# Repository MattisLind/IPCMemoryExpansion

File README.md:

# HP Integral PC Memory Expansion board

The HP Integral PC was a portable 68000 UNIX based computer introduced in 1984. The computer included a floppy drive as mass storage and a printer was built in. The screen was a electroluminicent screen. The computer has a HPIB connector to attach to external devices. External disks can be attached through HPIB.

The computer has a two expansion slot where various peripherals can be installed. For example serial boards or memory expansion boards. It was also possible to install ROM boards. The software engineering ROM has 2Mbyte of ROM expansion and when installed appear as 8 disk devices in the Unix system.

The project aims at creating a 7M RAM and 8M ROM memory expansion to the HP Integral computer. RAM is implemented using a single SRAM chip and ROM is implemented using a single NOR FLASH ROM chip. DIP-switches are used to map the ROM into the various ROM areas of the Integral.

## Levelshifting

All signals are level shifted from 5V TTL to 3.3V LVTTL using six 74LVC245 which has 5V tolerant inputs. The two open-collector signals, NBDTACK and NBIMA is handled by 1 74LS38 chip.

## Address decoding

A Xilinx XC2C32A CPLD is used for all address decoding and ROM remapping. The VHDL is provided [here](https://raw.githubusercontent.com/MattisLind/IPCMemoryExpansion/main/XILINX/IntegralMemExp/main.vhd).

## DIPSWITCH

The board is using a piano-type dipswitch for easy access from the side. When the switch is in the up position in corresponds to the off condition or digital 1 signal. When the switch is in the down position this corresponds to a on condition or 0 signal. X means that the position of the switch is irrelevant.

DIPSW0 to DIPSW5 is used for controlling the ROM mapping in the address space.

DIPSW7 is used for enabling and disabling the busdrivers and DIPSW6 is connected to RESET of the processor. Thus the processor portion can be completely disabled when both these switches are pushed down (on). They should be in the UP (off) position so that the processor runs and can access the memory when trying to upload to the flash memory onboard. When used in the Integral PC they should be in the DOWN (on) position to stop the processor and disable processor access to the memory.

## ROM
The mapping of the FLASH ROM memory is controlled by six dipswitches as follows:

| Integral address range | DIPSW0 | DIPSW1 | DIPSW2 | DIPSW3 | DIPSW4 | DIPSW5 | Flash memory range | Used for |
|------------------------|--------|--------|--------|--------|--------|--------|--------------------|----------|
| 000000 - 07FFFF        |   Down(0)    |   Down(0)    |   X    |   X    |   X    |   X    |  000000-07FFFF     | SYS V ROM|
| 000000 - 07FFFF        |   Down(0)    |   Up(1)    |   X    |   X    |   X    |   X    |  080000-0FFFFF     | DiagA ROM|
| 000000 - 07FFFF        |   Up(1)    |   Down(0)    |   X    |   X    |   X    |   X    |  100000-17FFFF     | DiagB ROM|
| 000000 - 07FFFF        |   Up(1)    |   Up(1)    |   X    |   X    |   X    |   X    |  NONE    | Internal ROM used |
| 080000 - 0FFFFF        |   X    |   X    |   Down(0)    |   X    |   X    |   X    |  NONE     | NONE |
| 080000 - 0FFFFF        |   X    |   X    |   Up(1)    |   X    |   X    |   X    |  180000-1FFFFF     | BASIC ROM |
| 100000 - 1FFFFF        |   X    |   X    |   X    |   X    |   X    |   Down(0)    |  NONE              |           |
| 100000 - 1FFFFF        |   X    |   X    |   X    |   X    |   X    |   Up(1)    |  600000-6FFFFF     | AUX ROM 3|
| 200000 - 3FFFFF        |   X    |   X    |   X    |   Down(0)    |   Down(0)    |   X    |  200000-3FFFFF     | SE ROM |
| 200000 - 3FFFFF        |   X    |   X    |   X    |   Down(0)    |   Up(1)    |   X    |  400000-5FFFFF     | AUX ROM 1|
| 200000 - 3FFFFF        |   X    |   X    |   X    |   Up(1)    |   X    |   X    |  NONE     | NONE |
| 300000 - 4FFFFF        |   X    |   X    |   X    |   X    |   X    |   Down(0)    |  NONE     | NONE |
| 300000 - 4FFFFF        |   X    |   X    |   X    |   X    |   X    |   Up(1)    |  700000-7FFFFF     | AUX ROM 2 |

There is a STM32F407ZET SoC makes the board look like a USB stick when the USB port is connected to a host computer. 

The ROM is implemented in one single 8 Mbyte SST38VF6401 chip.

## RAM

Normally Integral memory is implemented using memory board sized up to 1 MByte. Each memory board responds to a read port which provide an ID for the board and a writable base address register. The Integral will use these to identfiy each memory board and configure its starting address. However the memory sizing of HP-UX system is completely independent of the memory configuration descibed preiously meaning that these configuaration is not necessary to get the Integral to detect the full memory. This has been verified using the MAME emulation of the Integral.

All this obviously that it would be very much easier to implement a RAM expansion board since it only requires that it would match the RAM address range 800000-EFFFFF.

The RAM is implemented in one single AS6C6416 4M x 16 SRAM memory chip. 

## Testing and design fault finding.

Obviously when testing the board for the first time it didn't work at all. Of course I tested many different ways to get it working. But in the end I think that one main problem was the use of UDS/LDS instead of AS strobe. On the standard 68000 that would probably have worked just fine. But on the HP Integral he AS strobe is not at all the AS strobe from the processor. It has gone through plenty of logic until the AS signal found in the expasion connector is generated. Thus the use of the AS signal is a must. Gating with that signal made the RAM expansio work fine.

Since the 74LVC245 inputs are CMOS there wil be no current flowing towards the expansion board. When I attached a bus extender board to be able to measure on the board the added buslength seemed to cause trouble. Adding bus terminating resistors at the 74LVC245 inputs seemed to fix the issue. To better adapt the 74LVC245 driver to the bus impedance a low ohm resistor was inserted in the bus line path for the data bus.

All these changes resulted in a second spin of the board.

## Spin 2

Spin 1 became quite messy when trying to fix all small problems so I decided on a spin 2. I also added test points to make it easier to measure on the board, a major issue on the first spin was that it was so hard to take measurements. After spin 2 came back from the JLCPCB I found that it was virtually impossible to get hold of the STM32 chip and the CPLD, so the project got dormant until sping 2023 when I eventually was able to order chips.

There were some small changes made to the CPLD VHDL code for spin 2 ~~which to this date has not yet been tested (2023-07-24). I hope to be able to test the board soon.~~
Spin 2 has now been tested and appears to work correctly. Follow instructions further down to install the board.

## Firmware

There are two firmwares. One Arduino style .ino-sketch which I used for testing and the a STM32Cube applicaton that is the production code. I used STM32 because it was so simple to wrap up the USB mass storage stuff. The code essentially enables the FSMC controller of the chip and enables the USB mass storage code, then it responds to read and writes to the memory. While the USB-cable is connected the green LED will blink. The yellow LED will blink when a read is performed and the red will blink when a write is performed.

## Installation

There are three steps that need to be taken to install the all needed software/firmware to get the board running.
1. Program the CPLD
2. Install the STM32 firmware
3. Upload integral software to the board

For all these steps the USB connector of the board need to be connected to a USB outlet to the computer. This will thus supply the board with power and in the third step also make the board able to communicate with the host.

### Program the CPLD

The CPLD code is written in VHDL and I have used the Xilinx ISE version 14.7. In order to just install the existing JEDEC file provided in the repo it is only necessary to use the Impact tool in the Xilinx ISE suite. Download, start Impact, attach the Xilinx download cable and make sure that the device is detected. Then select the main.jed file and program the device.

### Install the STM32 firmware

You need both the STM32CubeIDE and STM32CubeProgrammer which has to be downloaded from the ST webpage. Use defaults when installing the software.

When installation is ready start STM32CubeIDE and select the "Open Projects from file System" option in the menu. Select the folder " Software/STM32CubeIDE/workspace_1.7.0 /HP IPC Memory Expansion/" in this repo. In the project menu, select the Build Configurations. This will open a submenu which where you can do "Set Active" Select "Release"

Now do "Build All" from the project menu and the full software will be built.

Now start the STM32CubeProgrammer software nd make sure the STM32 download canle is attached to the board and that power is supplied to the board using the USB cable. In this step DIPSW 6 and DIPSW 7 has to be in the up posistion.

Select the "HP IPC Memory Expansion.elf" binary in the Release folder and do a "Erase and program" operation.

### Uploading Integral software to the board

The idea is to use the Linux dd command to transfer the image-file generated by the build.sh shellscript in ROMS folder. When doing so the red and green LEDs should blink. It should also be possible to read back the content stored using dd and compare with the actual file. It is important to write the image to the topmost 8M of the USB device created when the board is connected over USB. The top 8M is mapped to the flash memory while the lower 8M is mapped to the SRAM.

Thus this command is needed to write the flash:

```
sudo dd if=flash_image.bin of=/dev/sd<x> bs=1k seek=8192
```
where ```/dev/sd<x>``` is the device that is allocated for the mass storage device that the board is acting as. Check using ```dmesg``` what device is created when it is plugged into the USB-port.

## Schematic 

## Install instructions by Carl Claunch

After spin 1 was completed I was not able to get components for spin 2 although the board had been fabricated. All this due to the post-covid semiconductor crunch. In July 2023 I got contacted by Carl who had been asked to help out to do the installation of the firmware. As we sorted out how topoerform the steps (which I had more or less forgotten since I initially designed it) he created a nice document which describes the steps do be done. I link it below:

[Install instructions by Carl Claunch](https://github.com/MattisLind/IPCMemoryExpansion/blob/main/HP%20Integral%20board%20instructions.pdf)

## BOM
This is a BOM for the spin 2 board:

| Component designator | Description | Mouser order number | Misc. |
|----------------------|-------------|---------------------|-------|
| R1,R5,R6,R7,R8,R9,R11,R14,R15| 10kOhm SMD 0805 |  -  |   |
| R2,R3,R4        | 330 Ohm SMD 0805 | - | |
| R10 | 1MOhm SMD 0805 | - | |
| R12,R13 | 22 Ohm SMD 0805 | - | |
| RN1,RN2,RN15,RN16 |  network 4 x bussed 56 Ohm THT | 652-4608X-2LF-56 | |
| RN3,RN4,RN5,RN6,RN11,RN12 | network 8 x star 3.9 KOhm  THT | 652-4609X-1LF-3.9K | |
| RN10 | network 5 x star 3.3 KOhm THT | 652-4606X-1LF-3.3K | |
| RN7,RN8,RN9,RN10,RN13,RN14 | network 8 x star 3.3 KOhm THT | 652-4609X-1LF-3.3K | |
| RN6 |  network 5 x star 3.9 KOhm | 652-4606X-1LF-3.9K | |
| C1,C2,C3,C5,C6,C7,C8 | 100 nF Ceramic THT, RM5 | - | |
| C4,C10 | 100 uF Electrolytic THT, RM 2.5 | - ||
| C9,C11,C12,C13,C14,C15,C16,C17,C18,<BR>C19,C20,C21,C27,C28,C29,C30,C31,C32 | 100 nF SMD 0805 | - ||
| C22,C25,C26| 2.2 uF   SMD, 0805 | - | C25 is on the underside just <BR>below the processor chip,<BR>close to C29. The silkscreen is a bit bad |
| C23,C24 | 22 pF     SMD, 0805 | - | |
| D1 | IN4148 SMD | 750-1N4148W-HF | Located on the top side <BR>close to the processor |
| D2 | LED green 3mm THT | 859-LTL-4231N | |
| D3 | LED yellow 3mm THT | 859-LTL-4251N | |
| D4 | LED red 3mm THT | 859-LTL-4221N | |
| D5,D6 | MBRS130L SMD, 2010 | 78-VS-MBRS130L-M35BT | |
| SW1 |  8 DIP switch - piano style THT | 774-1958MS | |
| U1,U2,U3,U4,U5,U10 | 74LVC245 THT | 595-SN74LVC245ANE4 | |
| U6 | XC2C32A SMD | 217-XC2C32A-6VQG44I | |
| U7 | SST38VF6401 SMD | 804-38VF64019CEKE | |
| U8 |  AS6C6416 SMD | 913-AS6C6416-55TIN | |
| U9 | STM32F407ZET  SMD | 511-STM32F407ZET7 | |
| U11 | 74LS38 THT | - | |
| U13 | AMS1117-3.3 SMD | 621-AZ1117CD-3.3TRG1 | Mounted on the bottom side |
| Y1 | Crystal 8 MHz | 815-ABL-8-B2 | |
| J1 | C64AC, 2 x 32 pin, 90 deg angle THT | 617-09732647801 |
| J2,J7,J13,J14,J15,J16,J17,J18,<BR>J19,J20,J21,J22,J23 | Test points | - | Normally not needed |
| J3 | Mini USB | 710-65100516121 | |
| J4 | 2 x 7 pin header, 90 deg angle, RM 2.54 | - | JTAG for Xilinx CPLD |
| J5 | 2 x 10 pin header, 90 deg angle, RM 2.54 | 710-61202021721 | JTAG for STM32 |
| J6 | 3 pin header, 90 deg angle, RM 2.54 | 538-22-28-8031 | Serial output |

## Links

[HP Museum page on the Integral PC](http://www.hpmuseum.net/display_item.php?hw=122)
<BR>[Peter Johnsons page on the Integral PC](http://www.coho.org/~pete/IPC/integral.html)

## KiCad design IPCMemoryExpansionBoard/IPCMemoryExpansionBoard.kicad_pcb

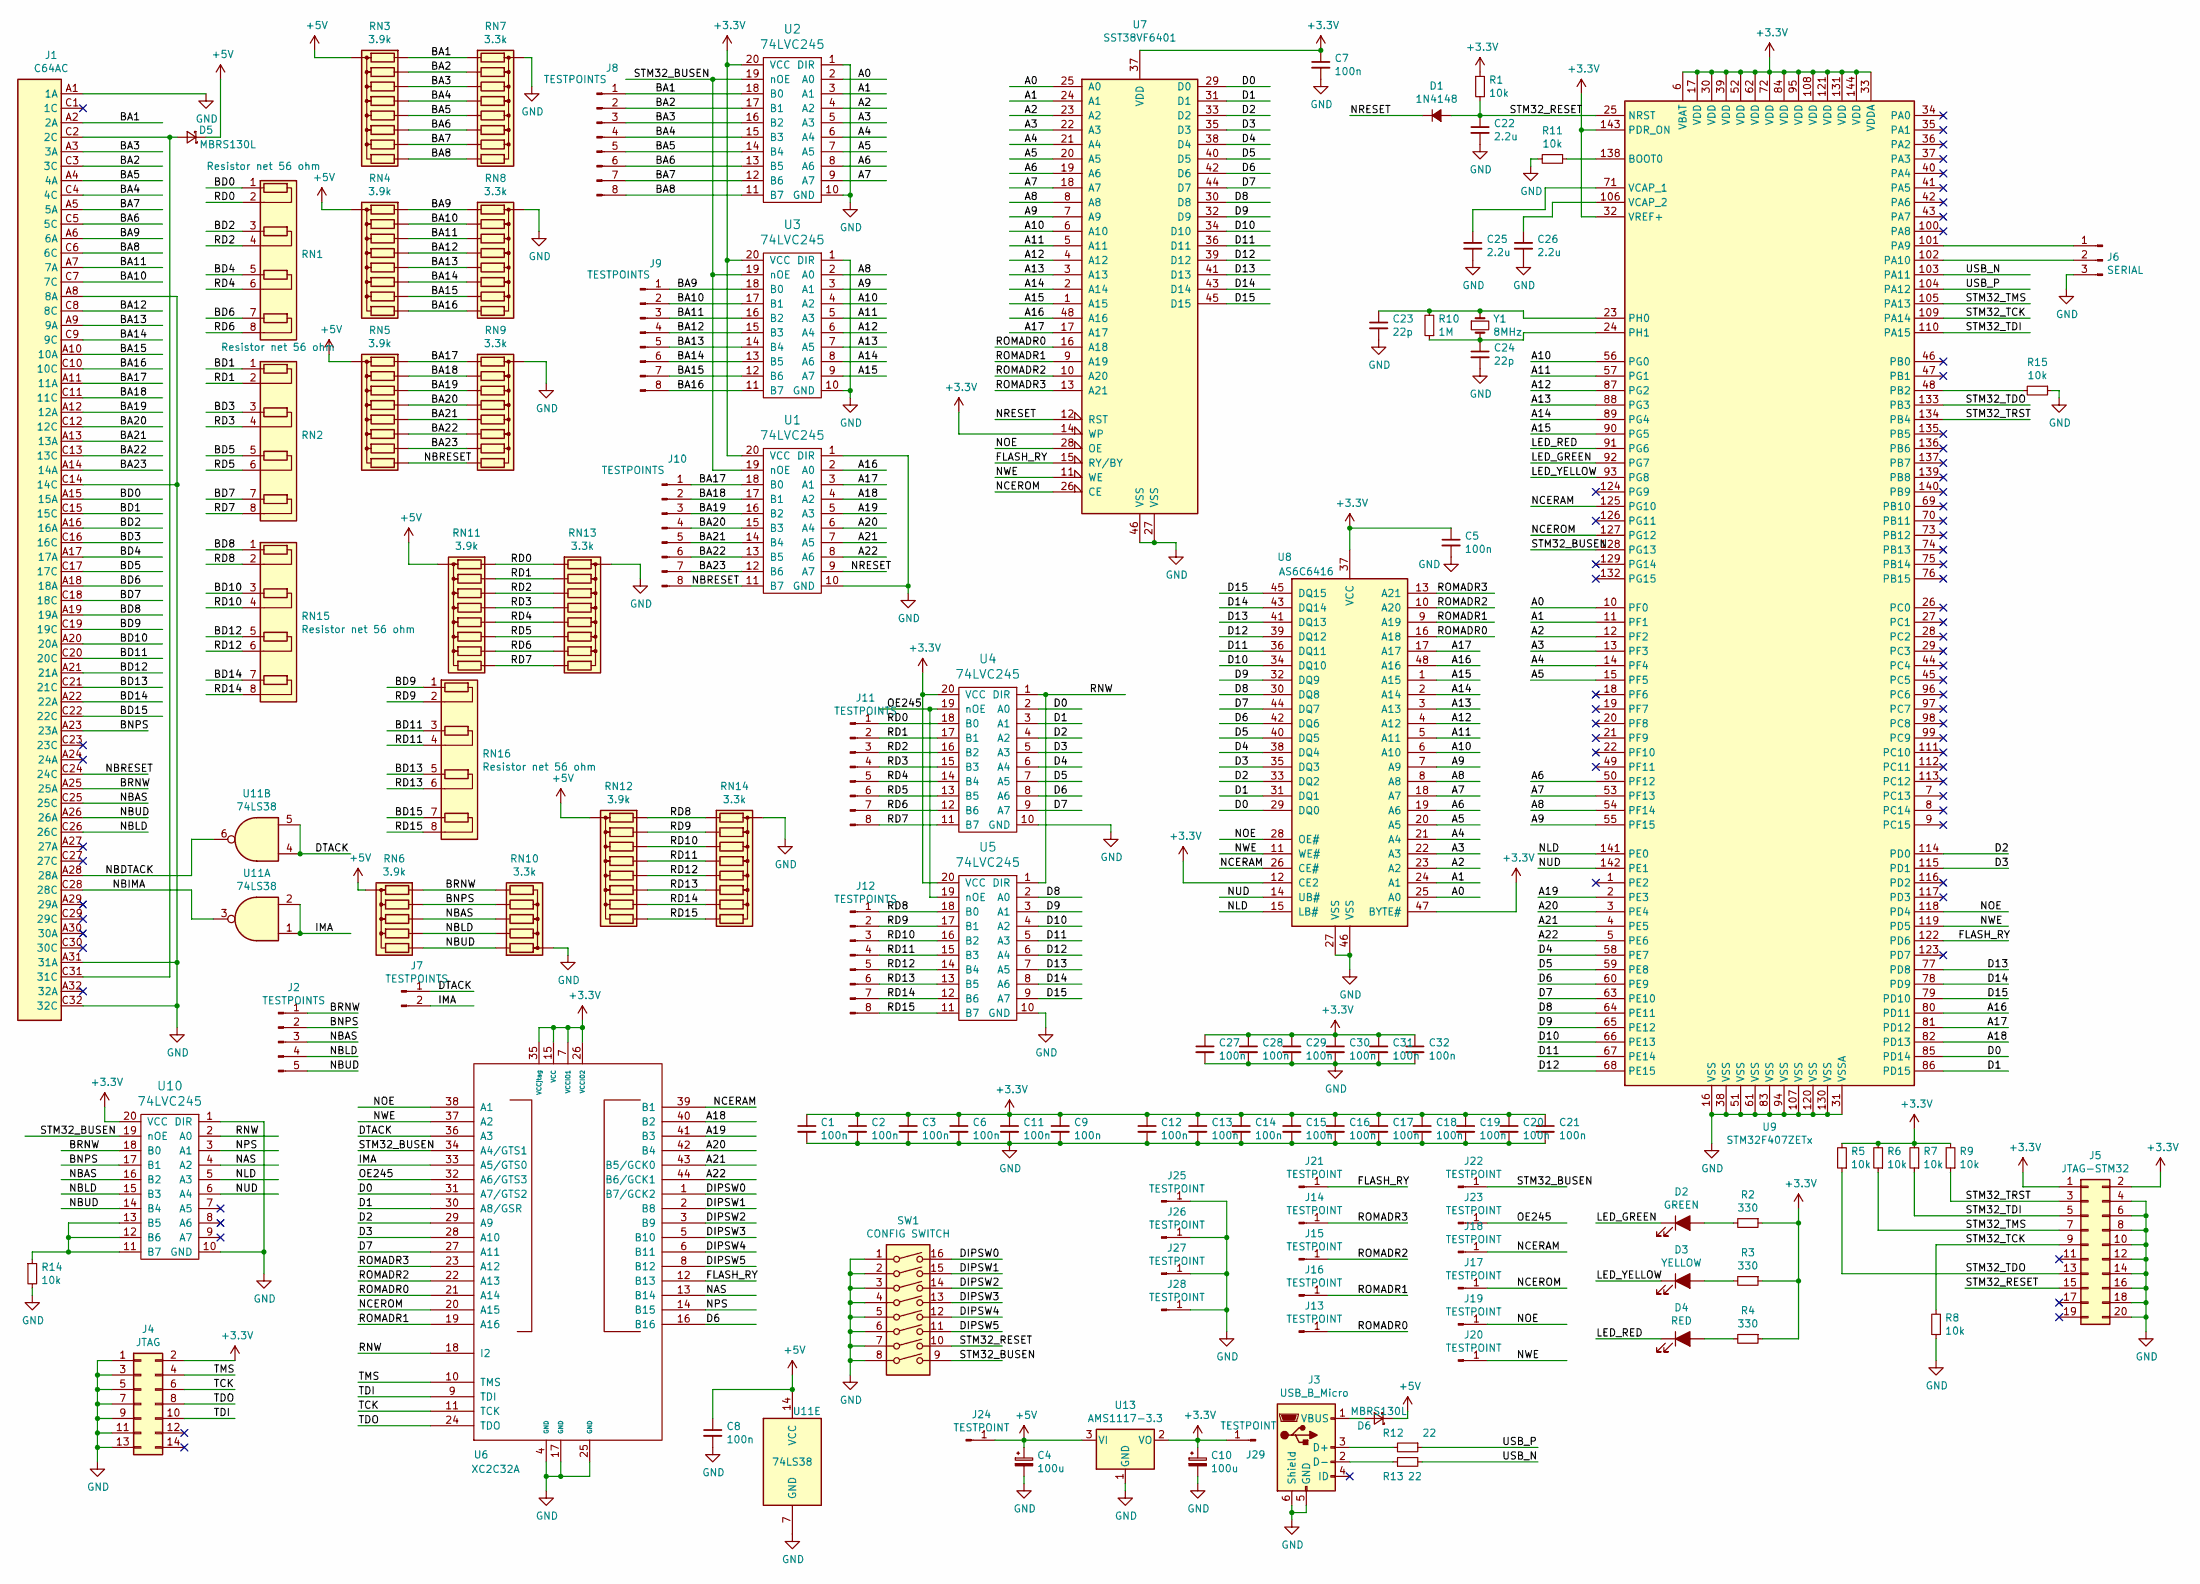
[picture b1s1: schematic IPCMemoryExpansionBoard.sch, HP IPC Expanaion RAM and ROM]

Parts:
C1, C2, C3, C5, C6, C7, C8: 100n; C_Disc_D4.3mm_W1.9mm_P5.00mm
C4, C10: 100u; CP_Radial_D5.0mm_P2.50mm
C9, C11, C12, C13, C14, C15, C16, C17, C18, C19, C20, C21, C27, C28, C29, C30, C31, C32: 100n; C_0805_2012Metric_Pad1.15x1.40mm_HandSolder
C22, C25, C26: 2.2u; C_0805_2012Metric_Pad1.15x1.40mm_HandSolder
C23, C24: 22p; C_0805_2012Metric_Pad1.15x1.40mm_HandSolder
D1: 1N4148; D_SOD-123
D2: GREEN; LED_D3.0mm_Horizontal_O1.27mm_Z2.0mm
D3: YELLOW; LED_D3.0mm_Horizontal_O1.27mm_Z2.0mm
D4: RED; LED_D3.0mm_Horizontal_O1.27mm_Z2.0mm
D5, D6: MBRS130L; D_SMB_Handsoldering
J1: C64AC; DIN41612_C_2x32_Male_Horizontal_THT
J2: TESTPOINTS; PinHeader_1x05_P2.54mm_Vertical
J3: USB_B_Micro; USB_Mini-B_Lumberg_2486_01_Horizontal
J4: JTAG; IDC-Header_2x07_P2.54mm_Horizontal
J5: JTAG-STM32; IDC-Header_2x10_P2.54mm_Horizontal
J6: SERIAL; PinHeader_1x03_P2.54mm_Horizontal
J7: TESTPOINTS; PinHeader_1x02_P2.54mm_Vertical
J8, J9, J10, J11, J12: TESTPOINTS; PinHeader_1x08_P2.54mm_Vertical
J13, J14, J15, J16, J17, J18, J19, J20, J21, J22, J23, J24, J25, J26, J27, J28, J29: TESTPOINT; PinHeader_1x01_P2.54mm_Vertical
R1, R5, R6, R7, R8, R9, R11, R14, R15: 10k; R_0805_2012Metric_Pad1.15x1.40mm_HandSolder
R2, R3, R4: 330; R_0805_2012Metric_Pad1.15x1.40mm_HandSolder
R10: 1M; R_0805_2012Metric_Pad1.15x1.40mm_HandSolder
R12, R13: 22; R_0805_2012Metric_Pad1.15x1.40mm_HandSolder
RN1, RN2, RN15, RN16: Resistor net 56 ohm; R_Array_SIP8
RN3, RN4, RN5, RN11, RN12: 3.9k; R_Array_SIP9
RN6: 3.9k; R_Array_SIP6
RN7, RN8, RN9, RN13, RN14: 3.3k; R_Array_SIP9
RN10: 3.3k; R_Array_SIP6
SW1: CONFIG SWITCH; DIP-16_W7.62mm
U1, U2, U3, U4, U5, U10: 74LVC245; DIP-20_W7.62mm
U6: XC2C32A; TQFP-44_10x10mm_P0.8mm
U7: SST38VF6401; TSOP-I-48_18.4x12mm_P0.5mm
U8: AS6C6416; TSOP-I-48_18.4x12mm_P0.5mm
U9: STM32F407ZETx; LQFP-144_20x20mm_P0.5mm
U11: 74LS38; DIP-14_W7.62mm
U13: AMS1117-3.3; SOT-223-3_TabPin2
Y1: 8MHz; Crystal_HC49-U_Vertical

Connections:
+3V3: C1.1, C2.1, C3.1, C5.1, C6.1, C7.1, C9.1, C10.1, C11.1, C12.1, C13.1, C14.1, C15.1, C16.1, C17.1, C18.1, C19.1, C20.1, C21.1, C27.1, C28.1, C29.1, C30.1, C31.1, C32.1, J4.2, J5.1, J5.2, J29.1, R1.1, R2.1, R3.1, R4.1, R5.2, R6.2, R7.2, R9.2, U1.20 (VCC), U2.20 (VCC), U3.20 (VCC), U4.20 (VCC), U5.20 (VCC), U6.7 (VCCIO1), U6.15 (VCC), U6.26 (VCCIO2), U6.35 (VCCjtag), U7.14 (WP), U7.37 (VDD), U8.12 (CE2), U8.37 (VCC), U8.47 (BYTE#), U9.6 (VBAT), U9.17 (VDD), U9.30 (VDD), U9.32 (VREF+), U9.33 (VDDA), U9.39 (VDD), U9.52 (VDD), U9.62 (VDD), U9.72 (VDD), U9.84 (VDD), U9.95 (VDD), U9.108 (VDD), U9.121 (VDD), U9.131 (VDD), U9.143 (PDR_ON), U9.144 (VDD), U10.20 (VCC), U13.2 (VO)
+5V: C4.1, C8.1, D5.1 (K), D6.1 (K), J24.1, RN3.1 (common), RN4.1 (common), RN5.1 (common), RN6.1 (common), RN11.1 (common), RN12.1 (common), U11.14 (VCC), U13.3 (VI)
/A0: U2.2 (A0), U7.25 (A0), U8.25 (A0), U9.10 (PF0)
/A1: U2.3 (A1), U7.24 (A1), U8.24 (A1), U9.11 (PF1)
/A2: U2.4 (A2), U7.23 (A2), U8.23 (A2), U9.12 (PF2)
/A3: U2.5 (A3), U7.22 (A3), U8.22 (A3), U9.13 (PF3)
/A4: U2.6 (A4), U7.21 (A4), U8.21 (A4), U9.14 (PF4)
/A5: U2.7 (A5), U7.20 (A5), U8.20 (A5), U9.15 (PF5)
/A6: U2.8 (A6), U7.19 (A6), U8.19 (A6), U9.50 (PF12)
/A7: U2.9 (A7), U7.18 (A7), U8.18 (A7), U9.53 (PF13)
/A8: U3.2 (A0), U7.8 (A8), U8.8 (A8), U9.54 (PF14)
/A9: U3.3 (A1), U7.7 (A9), U8.7 (A9), U9.55 (PF15)
/A10: U3.4 (A2), U7.6 (A10), U8.6 (A10), U9.56 (PG0)
/A11: U3.5 (A3), U7.5 (A11), U8.5 (A11), U9.57 (PG1)
/A12: U3.6 (A4), U7.4 (A12), U8.4 (A12), U9.87 (PG2)
/A13: U3.7 (A5), U7.3 (A13), U8.3 (A13), U9.88 (PG3)
/A14: U3.8 (A6), U7.2 (A14), U8.2 (A14), U9.89 (PG4)
/A15: U3.9 (A7), U7.1 (A15), U8.1 (A15), U9.90 (PG5)
/A16: U1.2 (A0), U7.48 (A16), U8.48 (A16), U9.80 (PD11)
/A17: U1.3 (A1), U7.17 (A17), U8.17 (A17), U9.81 (PD12)
/A18: U1.4 (A2), U6.40 (B2), U9.82 (PD13)
/A19: U1.5 (A3), U6.41 (B3), U9.2 (PE3)
/A20: U1.6 (A4), U6.42 (B4), U9.3 (PE4)
/A21: U1.7 (A5), U6.43 (B5/GCK0), U9.4 (PE5)
/A22: U1.8 (A6), U6.44 (B6/GCK1), U9.5 (PE6)
/BA1: J1.A2 (2A), J8.1, RN3.2 (R1), RN7.2 (R1), U2.18 (B0)
/BA2: J1.C3 (3C), J8.2, RN3.3 (R2), RN7.3 (R2), U2.17 (B1)
/BA3: J1.A3 (3A), J8.3, RN3.4 (R3), RN7.4 (R3), U2.16 (B2)
/BA4: J1.C4 (4C), J8.4, RN3.5 (R4), RN7.5 (R4), U2.15 (B3)
/BA5: J1.A4 (4A), J8.5, RN3.6 (R5), RN7.6 (R5), U2.14 (B4)
/BA6: J1.C5 (5C), J8.6, RN3.7 (R6), RN7.7 (R6), U2.13 (B5)
/BA7: J1.A5 (5A), J8.7, RN3.8 (R7), RN7.8 (R7), U2.12 (B6)
/BA8: J1.C6 (6C), J8.8, RN3.9 (R8), RN7.9 (R8), U2.11 (B7)
/BA9: J1.A6 (6A), J9.1, RN4.2 (R1), RN8.2 (R1), U3.18 (B0)
/BA10: J1.C7 (7C), J9.2, RN4.3 (R2), RN8.3 (R2), U3.17 (B1)
/BA11: J1.A7 (7A), J9.3, RN4.4 (R3), RN8.4 (R3), U3.16 (B2)
/BA12: J1.C8 (8C), J9.4, RN4.5 (R4), RN8.5 (R4), U3.15 (B3)
/BA13: J1.A9 (9A), J9.5, RN4.6 (R5), RN8.6 (R5), U3.14 (B4)
/BA14: J1.C9 (9C), J9.6, RN4.7 (R6), RN8.7 (R6), U3.13 (B5)
/BA15: J1.A10 (10A), J9.7, RN4.8 (R7), RN8.8 (R7), U3.12 (B6)
/BA16: J1.C10 (10C), J9.8, RN4.9 (R8), RN8.9 (R8), U3.11 (B7)
/BA17: J1.A11 (11A), J10.1, RN5.2 (R1), RN9.2 (R1), U1.18 (B0)
/BA18: J1.C11 (11C), J10.2, RN5.3 (R2), RN9.3 (R2), U1.17 (B1)
/BA19: J1.A12 (12A), J10.3, RN5.4 (R3), RN9.4 (R3), U1.16 (B2)
/BA20: J1.C12 (12C), J10.4, RN5.5 (R4), RN9.5 (R4), U1.15 (B3)
/BA21: J1.A13 (13A), J10.5, RN5.6 (R5), RN9.6 (R5), U1.14 (B4)
/BA22: J1.C13 (13C), J10.6, RN5.7 (R6), RN9.7 (R6), U1.13 (B5)
/BA23: J1.A14 (14A), J10.7, RN5.8 (R7), RN9.8 (R7), U1.12 (B6)
/BD0: J1.A15 (15A), RN1.1 (R1.1)
/BD1: J1.C15 (15C), RN2.1 (R1.1)
/BD2: J1.A16 (16A), RN1.3 (R2.1)
/BD3: J1.C16 (16C), RN2.3 (R2.1)
/BD4: J1.A17 (17A), RN1.5 (R3.1)
/BD5: J1.C17 (17C), RN2.5 (R3.1)
/BD6: J1.A18 (18A), RN1.7 (R4.1)
/BD7: J1.C18 (18C), RN2.7 (R4.1)
/BD8: J1.A19 (19A), RN15.1 (R1.1)
/BD9: J1.C19 (19C), RN16.1 (R1.1)
/BD10: J1.A20 (20A), RN15.3 (R2.1)
/BD11: J1.C20 (20C), RN16.3 (R2.1)
/BD12: J1.A21 (21A), RN15.5 (R3.1)
/BD13: J1.C21 (21C), RN16.5 (R3.1)
/BD14: J1.A22 (22A), RN15.7 (R4.1)
/BD15: J1.C22 (22C), RN16.7 (R4.1)
/BNPS: J1.A23 (23A), J2.2, RN6.3 (R2), RN10.5 (R4), U10.17 (B1)
/BRNW: J1.A25 (25A), J2.1, RN6.2 (R1), RN10.6 (R5), U10.18 (B0)
/D0: U4.2 (A0), U6.31 (A7/GTS2), U7.29 (D0), U8.29 (DQ0), U9.85 (PD14)
/D1: U4.3 (A1), U6.30 (A8/GSR), U7.31 (D1), U8.31 (DQ1), U9.86 (PD15)
/D2: U4.4 (A2), U6.29 (A9), U7.33 (D2), U8.33 (DQ2), U9.114 (PD0)
/D3: U4.5 (A3), U6.28 (A10), U7.35 (D3), U8.35 (DQ3), U9.115 (PD1)
/D4: U4.6 (A4), U7.38 (D4), U8.38 (DQ4), U9.58 (PE7)
/D5: U4.7 (A5), U7.40 (D5), U8.40 (DQ5), U9.59 (PE8)
/D6: U4.8 (A6), U6.16 (B16), U7.42 (D6), U8.42 (DQ6), U9.60 (PE9)
/D7: U4.9 (A7), U6.27 (A11), U7.44 (D7), U8.44 (DQ7), U9.63 (PE10)
/D8: U5.2 (A0), U7.30 (D8), U8.30 (DQ8), U9.64 (PE11)
/D9: U5.3 (A1), U7.32 (D9), U8.32 (DQ9), U9.65 (PE12)
/D10: U5.4 (A2), U7.34 (D10), U8.34 (DQ10), U9.66 (PE13)
/D11: U5.5 (A3), U7.36 (D11), U8.36 (DQ11), U9.67 (PE14)
/D12: U5.6 (A4), U7.39 (D12), U8.39 (DQ12), U9.68 (PE15)
/D13: U5.7 (A5), U7.41 (D13), U8.41 (DQ13), U9.77 (PD8)
/D14: U5.8 (A6), U7.43 (D14), U8.43 (DQ14), U9.78 (PD9)
/D15: U5.9 (A7), U7.45 (D15), U8.45 (DQ15), U9.79 (PD10)
/DIPSW0: SW1.16, U6.1 (B7/GCK2)
/DIPSW1: SW1.15, U6.2 (B8)
/DIPSW2: SW1.14, U6.3 (B9)
/DIPSW3: SW1.13, U6.5 (B10)
/DIPSW4: SW1.12, U6.6 (B11)
/DIPSW5: SW1.11, U6.8 (B12)
/DTACK: J7.1, U6.36 (A3), U11.4, U11.5
/FLASH_RY: J21.1, U6.12 (B13), U7.15 (RY/BY), U9.122 (PD6)
/IMA: J7.2, U6.33 (A5/GTS0), U11.1, U11.2
/LED_GREEN: D2.1 (K), U9.92 (PG7)
/LED_RED: D4.1 (K), U9.91 (PG6)
/LED_YELLOW: D3.1 (K), U9.93 (PG8)
/NAS: U6.13 (B14), U10.4 (A2)
/NBAS: J1.C25 (25C), J2.3, RN6.4 (R3), RN10.4 (R3), U10.16 (B2)
/NBDTACK: J1.A28 (28A), U11.6
/NBIMA: J1.C28 (28C), U11.3
/NBLD: J1.C26 (26C), J2.4, RN6.5 (R4), RN10.3 (R2), U10.15 (B3)
/NBRESET: J1.C24 (24C), J10.8, RN5.9 (R8), RN9.9 (R8), U1.11 (B7)
/NBUD: J1.A26 (26A), J2.5, RN6.6 (R5), RN10.2 (R1), U10.14 (B4)
/NCERAM: J18.1, U6.39 (B1), U8.26 (CE#), U9.125 (PG10)
/NCEROM: J17.1, U6.20 (A15), U7.26 (CE), U9.127 (PG12)
/NLD: U8.15 (LB#), U9.141 (PE0), U10.5 (A3)
/NOE: J19.1, U6.38 (A1), U7.28 (OE), U8.28 (OE#), U9.118 (PD4)
/NPS: U6.14 (B15), U10.3 (A1)
/NRESET: D1.1 (K), U1.9 (A7), U7.12 (RST)
/NUD: U8.14 (UB#), U9.142 (PE1), U10.6 (A4)
/NWE: J20.1, U6.37 (A2), U7.11 (WE), U8.11 (WE#), U9.119 (PD5)
/OE245: J23.1, U4.19 (nOE), U5.19 (nOE), U6.32 (A6/GTS3)
/RD0: J11.1, RN1.2 (R1.2), RN11.2 (R1), RN13.2 (R1), U4.18 (B0)
/RD1: J11.2, RN2.2 (R1.2), RN11.3 (R2), RN13.3 (R2), U4.17 (B1)
/RD2: J11.3, RN1.4 (R2.2), RN11.4 (R3), RN13.4 (R3), U4.16 (B2)
/RD3: J11.4, RN2.4 (R2.2), RN11.5 (R4), RN13.5 (R4), U4.15 (B3)
/RD4: J11.5, RN1.6 (R3.2), RN11.6 (R5), RN13.6 (R5), U4.14 (B4)
/RD5: J11.6, RN2.6 (R3.2), RN11.7 (R6), RN13.7 (R6), U4.13 (B5)
/RD6: J11.7, RN1.8 (R4.2), RN11.8 (R7), RN13.8 (R7), U4.12 (B6)
/RD7: J11.8, RN2.8 (R4.2), RN11.9 (R8), RN13.9 (R8), U4.11 (B7)
/RD8: J12.1, RN12.2 (R1), RN14.2 (R1), RN15.2 (R1.2), U5.18 (B0)
/RD9: J12.2, RN12.3 (R2), RN14.3 (R2), RN16.2 (R1.2), U5.17 (B1)
/RD10: J12.3, RN12.4 (R3), RN14.4 (R3), RN15.4 (R2.2), U5.16 (B2)
/RD11: J12.4, RN12.5 (R4), RN14.5 (R4), RN16.4 (R2.2), U5.15 (B3)
/RD12: J12.5, RN12.6 (R5), RN14.6 (R5), RN15.6 (R3.2), U5.14 (B4)
/RD13: J12.6, RN12.7 (R6), RN14.7 (R6), RN16.6 (R3.2), U5.13 (B5)
/RD14: J12.7, RN12.8 (R7), RN14.8 (R7), RN15.8 (R4.2), U5.12 (B6)
/RD15: J12.8, RN12.9 (R8), RN14.9 (R8), RN16.8 (R4.2), U5.11 (B7)
/RNW: U4.1 (DIR), U5.1 (DIR), U6.18 (I2), U10.2 (A0)
/ROMADR0: J13.1, U6.21 (A14), U7.16 (A18), U8.16 (A18)
/ROMADR1: J16.1, U6.19 (A16), U7.9 (A19), U8.9 (A19)
/ROMADR2: J15.1, U6.22 (A13), U7.10 (A20), U8.10 (A20)
/ROMADR3: J14.1, U6.23 (A12), U7.13 (A21), U8.13 (A21)
/STM32_BUSEN: J22.1, SW1.9, U1.19 (nOE), U2.19 (nOE), U3.19 (nOE), U6.34 (A4/GTS1), U9.128 (PG13), U10.19 (nOE)
/STM32_RESET: C22.1, D1.2 (A), J5.15, R1.2, SW1.10, U9.25 (NRST)
/STM32_TCK: J5.9, R8.2, U9.109 (PA14)
/STM32_TDI: J5.5, R7.1, U9.110 (PA15)
/STM32_TDO: J5.13, R5.1, U9.133 (PB3)
/STM32_TMS: J5.7, R6.1, U9.105 (PA13)
/STM32_TRST: J5.3, R9.1, U9.134 (PB4)
/TCK: J4.6, U6.11 (TCK)
/TDI: J4.10, U6.9 (TDI)
/TDO: J4.8, U6.24 (TDO)
/TMS: J4.4, U6.10 (TMS)
/USB_N: R13.2, U9.103 (PA11)
/USB_P: R12.1, U9.104 (PA12)
GND: C1.2, C2.2, C3.2, C4.2, C5.2, C6.2, C7.2, C8.2, C9.2, C10.2, C11.2, C12.2, C13.2, C14.2, C15.2, C16.2, C17.2, C18.2, C19.2, C20.2, C21.2, C22.2, C23.2, C24.2, C25.2, C26.2, C27.2, C28.2, C29.2, C30.2, C31.2, C32.2, J1.A1 (1A), J1.A8 (8A), J1.A31 (31A), J1.C14 (14C), J1.C32 (32C), J3.5 (GND), J3.6 (Shield), J4.1, J4.3, J4.5, J4.7, J4.9, J4.11, J4.13, J5.4, J5.6, J5.8, J5.10, J5.12, J5.14, J5.16, J5.18, J5.20, J6.3, J25.1, J26.1, J27.1, J28.1, R8.1, R11.2, R14.2, R15.1, RN7.1 (common), RN8.1 (common), RN9.1 (common), RN10.1 (common), RN13.1 (common), RN14.1 (common), SW1.1, SW1.2, SW1.3, SW1.4, SW1.5, SW1.6, SW1.7, SW1.8, U1.1 (DIR), U1.10 (GND), U2.1 (DIR), U2.10 (GND), U3.1 (DIR), U3.10 (GND), U4.10 (GND), U5.10 (GND), U6.4 (GND), U6.17 (GND), U6.25 (GND), U7.27 (VSS), U7.46 (VSS), U8.27 (VSS), U8.46 (VSS), U9.16 (VSS), U9.31 (VSSA), U9.38 (VSS), U9.51 (VSS), U9.61 (VSS), U9.83 (VSS), U9.94 (VSS), U9.107 (VSS), U9.120 (VSS), U9.130 (VSS), U10.1 (DIR), U10.10 (GND), U11.7 (GND), U13.1 (GND)
unnamed: C23.1, R10.2, U9.23 (PH0), Y1.1
unnamed: C24.1, R10.1, U9.24 (PH1), Y1.2
unnamed: C25.1, U9.71 (VCAP_1)
unnamed: C26.1, U9.106 (VCAP_2)
unnamed: D2.2 (A), R2.2
unnamed: D3.2 (A), R3.2
unnamed: D4.2 (A), R4.2
unnamed: D5.2 (A), J1.C2 (2C), J1.C31 (31C)
unnamed: D6.2 (A), J3.1 (VBUS)
unnamed: J3.2 (D-), R13.1
unnamed: J3.3 (D+), R12.2
unnamed: J6.1, U9.101 (PA9)
unnamed: J6.2, U9.102 (PA10)
unnamed: R11.1, U9.138 (BOOT0)
unnamed: R14.1, U10.11 (B7), U10.12 (B6), U10.13 (B5)
unnamed: R15.2, U9.48 (PB2)

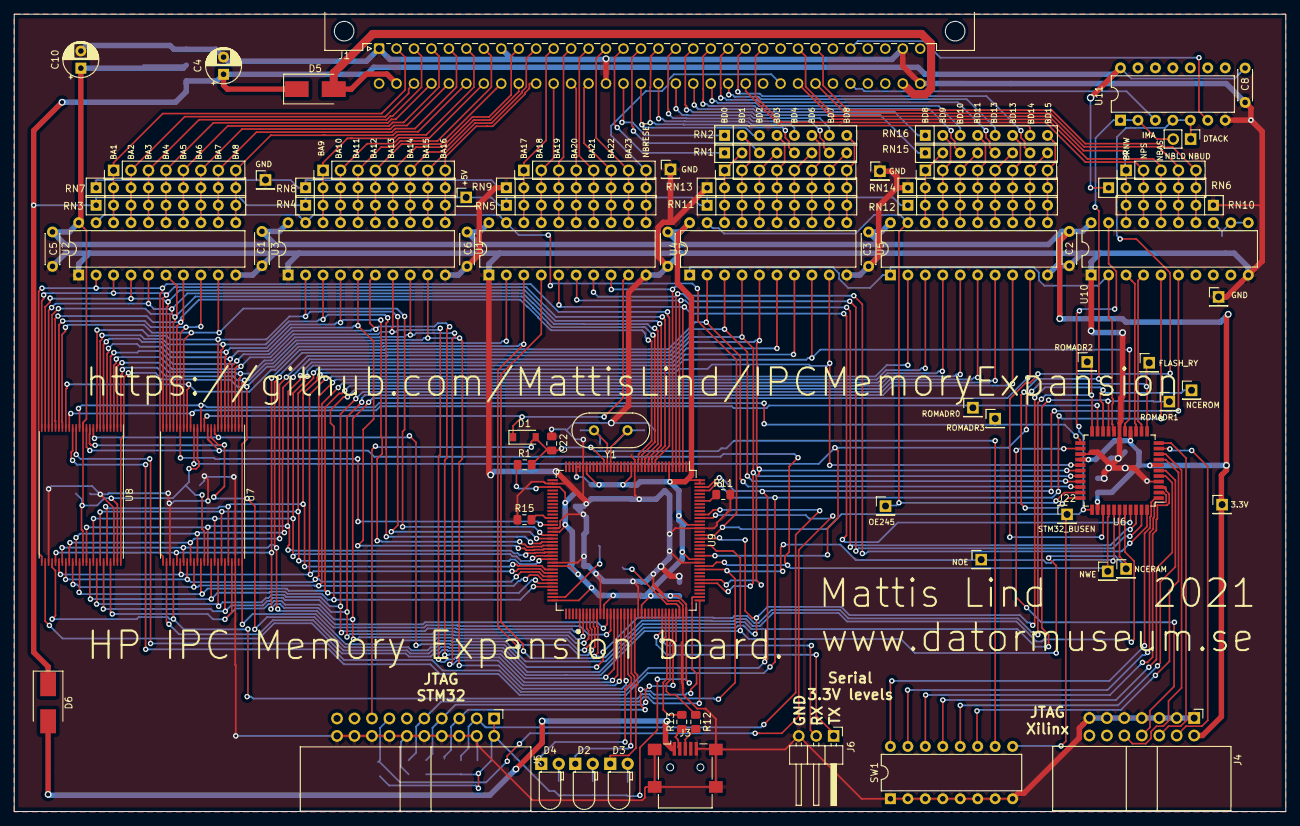
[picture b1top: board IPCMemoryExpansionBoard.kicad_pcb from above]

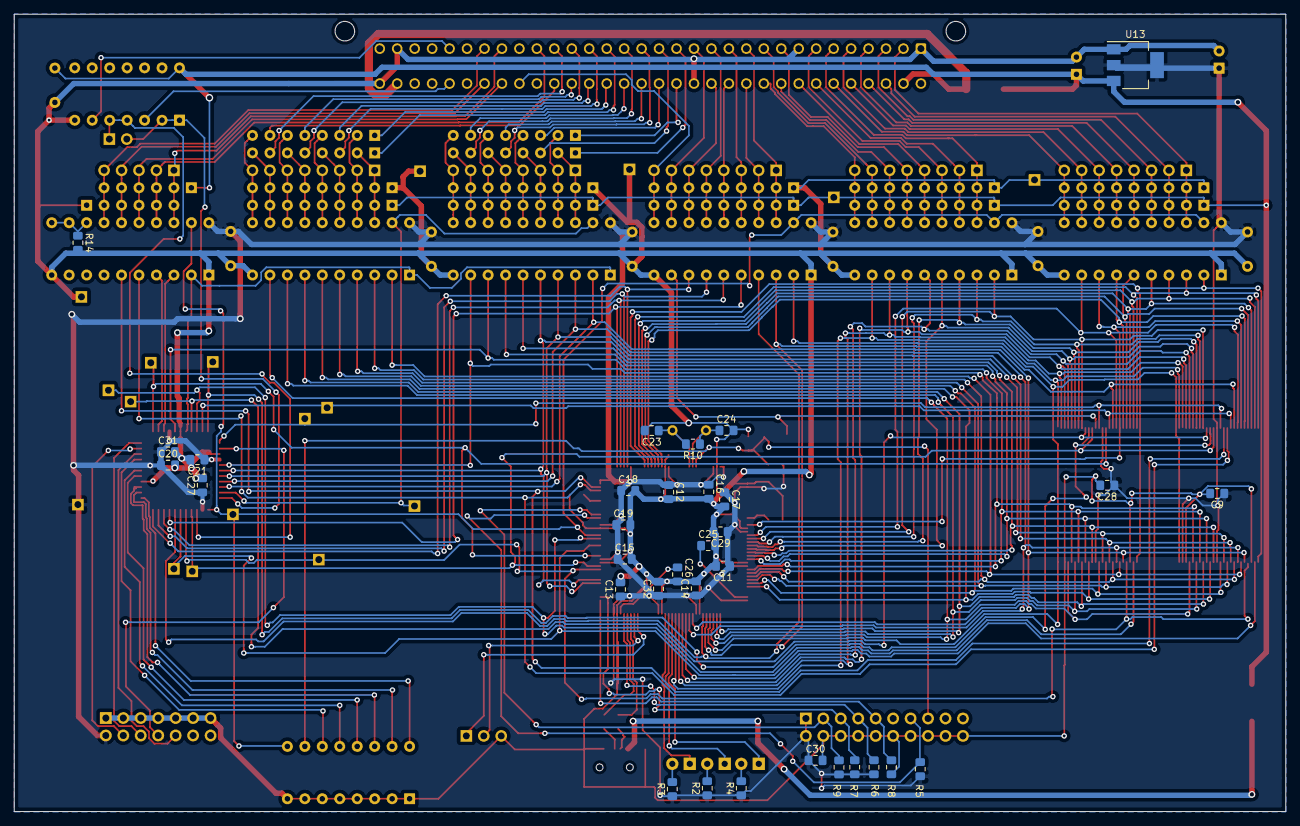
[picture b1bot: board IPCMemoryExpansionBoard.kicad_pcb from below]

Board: 2 copper layers, 185.0 x 116.0 mm, 112 parts (33 on the bottom side), 161 nets.

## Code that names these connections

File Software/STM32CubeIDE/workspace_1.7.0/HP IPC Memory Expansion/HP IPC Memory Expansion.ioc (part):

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Mcu.Name=STM32F407Z(E-G)Tx
Mcu.Package=LQFP144
Mcu.UserName=STM32F407ZETx
PA10.Mode=Asynchronous
PA10.Signal=USART1_RX
PA11.Mode=Device_Only
PA11.Signal=USB_OTG_FS_DM
PA12.Mode=Device_Only
PA12.Signal=USB_OTG_FS_DP
PA13.Mode=Serial_Wire
PA13.Signal=SYS_JTMS-SWDIO
PA14.Mode=Serial_Wire
PA14.Signal=SYS_JTCK-SWCLK
PA9.Mode=Asynchronous
PA9.Signal=USART1_TX
PD0.Signal=FSMC_D2_DA2
PD1.Signal=FSMC_D3_DA3
PD10.Signal=FSMC_D15_DA15
PD11.Signal=FSMC_A16_CLE
PD12.Signal=FSMC_A17_ALE
PD13.Signal=FSMC_A18
PD14.Signal=FSMC_D0_DA0
PD15.Signal=FSMC_D1_DA1
PD4.Signal=FSMC_NOE
PD5.Signal=FSMC_NWE
PD6.GPIOParameters=GPIO_Label
PD6.GPIO_Label=RY_WAIT
PD6.Signal=GPIO_Input
PD8.Signal=FSMC_D13_DA13
PD9.Signal=FSMC_D14_DA14
PE0.Signal=FSMC_NBL0
PE1.Signal=FSMC_NBL1
PE10.Signal=FSMC_D7_DA7
PE11.Signal=FSMC_D8_DA8
PE12.Signal=FSMC_D9_DA9
PE13.Signal=FSMC_D10_DA10
PE14.Signal=FSMC_D11_DA11
PE15.Signal=FSMC_D12_DA12
PE3.Signal=FSMC_A19
PE4.Signal=FSMC_A20
PE5.Signal=FSMC_A21
PE6.Signal=FSMC_A22
PE7.Signal=FSMC_D4_DA4
PE8.Signal=FSMC_D5_DA5
PE9.Signal=FSMC_D6_DA6
PF0.Signal=FSMC_A0
PF1.Signal=FSMC_A1
PF12.Signal=FSMC_A6
PF13.Signal=FSMC_A7
PF14.Signal=FSMC_A8
PF15.Signal=FSMC_A9
PF2.Signal=FSMC_A2
PF3.Signal=FSMC_A3
PF4.Signal=FSMC_A4
PF5.Signal=FSMC_A5
PG0.Signal=FSMC_A10
PG1.Signal=FSMC_A11
PG10.Mode=NorPsramChipSelect3_3
PG10.Signal=FSMC_NE3
PG12.Mode=NorPsramChipSelect4_4
PG12.Signal=FSMC_NE4
PG13.GPIOParameters=GPIO_Label
PG13.GPIO_Label=STM32_ENABLE
PG13.Signal=GPIO_Output
PG2.Signal=FSMC_A12
PG3.Signal=FSMC_A13
PG4.Signal=FSMC_A14
PG5.Signal=FSMC_A15
PG6.GPIOParameters=GPIO_Label,GPIO_ModeDefaultOutputPP
PG6.GPIO_Label=LED_RED
PG6.GPIO_ModeDefaultOutputPP=GPIO_MODE_OUTPUT_OD
PG6.Signal=GPIO_Output
PG7.GPIOParameters=GPIO_Label,GPIO_ModeDefaultOutputPP
PG7.GPIO_Label=LED_YELLOW
PG7.GPIO_ModeDefaultOutputPP=GPIO_MODE_OUTPUT_OD
PG7.Signal=GPIO_Output
PG8.GPIOParameters=GPIO_Label,GPIO_ModeDefaultOutputPP
PG8.GPIO_Label=LED_GREEN
PG8.GPIO_ModeDefaultOutputPP=GPIO_MODE_OUTPUT_OD
PG8.Signal=GPIO_Output
PH0-OSC_IN.Mode=HSE-External-Oscillator
PH0-OSC_IN.Signal=RCC_OSC_IN
PH1-OSC_OUT.Mode=HSE-External-Oscillator
PH1-OSC_OUT.Signal=RCC_OSC_OUT
RCC.HSE_VALUE=8000000
RCC.SYSCLKFreq_VALUE=168000000
RCC.SYSCLKSource=RCC_SYSCLKSOURCE_PLLCLK
board=custom

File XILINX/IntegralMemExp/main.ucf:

#PACE: Start of Constraints generated by PACE

#PACE: Start of PACE I/O Pin Assignments
NET "ADRIN<0>" LOC = P40 | IOSTANDARD = LVTTL | PULLUP;
NET "ADRIN<1>" LOC = P41 | IOSTANDARD = LVTTL | PULLUP;
NET "ADRIN<2>" LOC = P42 | IOSTANDARD = LVTTL | PULLUP;
NET "ADRIN<3>" LOC = P43 | IOSTANDARD = LVTTL | PULLUP;
NET "ADRIN<4>" LOC = P44 | IOSTANDARD = LVTTL | PULLUP;
NET "D0" LOC = P31 | IOSTANDARD = LVTTL ;
NET "D1" LOC = P30 | IOSTANDARD = LVTTL ;
NET "D2" LOC = P29 | IOSTANDARD = LVTTL ;
NET "D3" LOC = P28 | IOSTANDARD = LVTTL ;
NET "D7" LOC = P27 | IOSTANDARD = LVTTL ;
NET "DIPSW0" LOC = P1 | IOSTANDARD = LVTTL  | PULLUP ;
NET "DIPSW1" LOC = P2 | IOSTANDARD = LVTTL  | PULLUP ;
NET "DIPSW2" LOC = P3 | IOSTANDARD = LVTTL  | PULLUP ;
NET "DIPSW3" LOC = P5 | IOSTANDARD = LVTTL  | PULLUP ;
NET "DIPSW4" LOC = P6 | IOSTANDARD = LVTTL  | PULLUP ;
NET "DIPSW5" LOC = P8 | IOSTANDARD = LVTTL  | PULLUP ;
NET "DTACK" LOC = P36 | IOSTANDARD = LVTTL ;
NET "IMA" LOC = P33 | IOSTANDARD = LVTTL;
NET "NCERAM" LOC = P39 | IOSTANDARD = LVTTL  | PULLUP ;
NET "NCEROM" LOC = P20 | IOSTANDARD = LVTTL  | PULLUP ;
NET "FLASH_RY" LOC = P12 | IOSTANDARD = LVTTL | PULLUP;
NET "NAS" LOC = P13 | IOSTANDARD = LVTTL | PULLUP;
NET "NOE" LOC = P38 | IOSTANDARD = LVTTL  | PULLUP ;
NET "NPS" LOC = P14 | IOSTANDARD = LVTTL | PULLUP;
NET "D6" LOC = P16 | IOSTANDARD = LVTTL;
NET "NWE" LOC = P37 | IOSTANDARD = LVTTL  | PULLUP ;
NET "OE245" LOC = P32 | IOSTANDARD = LVTTL;
NET "RNW" LOC = P18 | IOSTANDARD = LVTTL | PULLUP ;
NET "ROMADR<0>" LOC = P21 | IOSTANDARD = LVTTL;
NET "ROMADR<1>" LOC = P19 | IOSTANDARD = LVTTL;
NET "ROMADR<2>" LOC = P22 | IOSTANDARD = LVTTL;
NET "ROMADR<3>" LOC = P23 | IOSTANDARD = LVTTL;
NET "STM32_BUSEN" LOC = P34 | IOSTANDARD = LVTTL  | PULLUP ;

#PACE: Start of PACE Area Constraints

#PACE: Start of PACE Prohibit Constraints

#PACE: End of Constraints generated by PACE

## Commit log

2021-04-01 Added Xilinx projec files .
2021-04-01 Added kicad schematic.
2021-04-01 Added pdf-file.
2021-04-03 Adding png of the schematic
2021-04-03 Added schematic.
2021-04-03 A lot of stuff added..
2021-04-25 Updates and fixes.
2021-08-23 Update schematic. Fixed PCB. Added zip for gerbers.
2021-09-14 Added testbench and fixed a few small issues in the VHDL code.
2021-09-14 Added the first steps towards a firmware.
2021-09-14 Small fixes to the PCB. RESET was short circuit to GND
2021-09-14 Refacto SRAM test. Started adding flash routines.
2021-09-14 Added ROMs and a digest of the SE ROM in pdf and rtf.
2021-09-15 Added Diag rom files
2021-09-18 Flash and SRAM testing.
2021-10-01 Added ready line. Small command line tool.
2021-10-01 Added more commands.
2021-10-11 Merged together into one file.
2021-10-11 Added a merged Diag file.
2021-10-11 Splitted up sys V / Tech Basic into two files.
2021-10-11 The tech BASIC ROM was wrong. Added a script that created the combined flash image.
2021-11-03 Fixed so that Diag ROMs ara aliased over the adress range. Updated build script to use original diag ROMS
2021-12-12 Started work on spin 2.
2021-12-12 Rotated pdf.
2021-12-12 Regenerated png.
2021-12-22 Made spin 2 of the board
2021-12-23 Added all the stm32cube files.
2021-12-23 Added new Xilinx files.
2021-12-23 New ino sketch
2022-01-03 Layout ready.
2023-07-18 Update README.md
    Removed mentioning SD card since it was removed in spin 2.
2023-08-06 Add correct info on the dd command.
    Add correct info on the dd command.
2023-08-06 /dev/sd<x> got lost
2023-08-06 Add main.jed
2023-08-06 Delete test.jed
    This file is probably obsolete. Replaced with main.jed
2023-08-07 Installation instructions.
    Installation instructions by Carl Claunch added
2023-09-13 Update README.md
    Add BOM
2023-09-13 Update README.md
    Added linebreaks
